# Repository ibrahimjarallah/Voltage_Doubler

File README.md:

# Voltage Doubler — NE555 Based PCB

> A compact, single-supply voltage doubler circuit built around the NE555 timer IC.  
> Designed and laid out in **KiCad 9.0** — schematic + 2-layer PCB with full fabrication outputs.

---

## 📸 3D Views

| Front | Back |
|:---:|:---:|
|  |  |

## 🖼️ PCB Layout (2D)

| Front | Back |
|:---:|:---:|
|  |  |

## 🟤 PCB Layout — Copper Fill (2D)

| Front | Back |
|:---:|:---:|
|  |  |

## 📐 Schematic

---

## ⚡ Specifications

| Parameter         | Value                        |
|-------------------|------------------------------|
| Input Voltage     | 5V DC                        |
| Output Voltage    | ~8.6V DC (no load)           |
| Topology          | Villard Cascade (diode-cap)  |
| Oscillator        | NE555 astable mode           |
| Oscillation Freq  | ~600 Hz                      |
| Output Ripple     | Dependent on load current    |
| PCB Layers        | 2                            |
| Designed With     | KiCad 9.0.7                  |

> **Note:** Output voltage sags under load due to 22µF storage capacitors and NE555 drive limitations.  
> Suitable for light-load, low-current applications.

---

## 🔧 How It Works

The **NE555** is configured in **astable (free-running) mode**, generating a ~600 Hz square wave set by:

- **R1** (10kΩ) and **R2** (33kΩ) — timing resistors
- **C1/C2** (10nF) — timing capacitors

This switching signal drives a **Villard cascade** charge pump:

1. On the rising edge, **C3** (22µF) charges through **D1** (1N4007)
2. On the falling edge, **C4** (22µF) charges to the sum of Vin + Vc3 through **D2** (1N4007)
3. Result: output voltage ≈ **2 × Vin − 2 × Vf** ≈ **8.6V** (where Vf ≈ 0.7V per diode)

---

## 📦 Bill of Materials

| ID | Designator | Description | Quantity | Footprint |
|----|------------|-------------|----------|-----------|
| 1 | U1 | NE555D Timer IC | 1 | SO-8 3.9×4.9mm P1.27mm |
| 2 | R1 | Resistor 10.0kΩ | 1 | Axial DIN0204 L3.6mm P5.08mm |
| 3 | R2 | Resistor 33.0kΩ | 1 | Axial DIN0204 L3.6mm P5.08mm |
| 4 | D1, D2 | Diode 1N4007 | 2 | D 5W P10.16mm Horizontal |
| 5 | C1, C2 | Capacitor 10nF (ceramic) | 2 | Disc D3.0mm W1.6mm P2.50mm |
| 6 | C3, C4 | Capacitor 22µF (electrolytic) | 2 | Radial D4.0mm H5.0mm P1.50mm |
| 7 | J1, J2 | 1×2 Pin Header connector | 2 | PinHeader 1×2 P1.00mm Horizontal |

---

## 📁 Repository Structure

```
Voltage_Doubler/
├── Voltage_Doubler.kicad_pro     # KiCad project file
├── Voltage_Doubler.kicad_sch     # Schematic
├── Voltage_Doubler.kicad_pcb     # PCB layout
├── Voltage_Doubler.kicad_dru     # Design rules
├── Voltage_Doubler.net           # Netlist
├── BOM/
│   └── Voltage_Doubler.csv       # Bill of materials
├── gerbers/                      # Fabrication Gerber files
│   ├── Voltage_Doubler-F_Cu.gbr
│   ├── Voltage_Doubler-B_Cu.gbr
│   ├── Voltage_Doubler-F_Mask.gbr
│   ├── Voltage_Doubler-B_Mask.gbr
│   ├── Voltage_Doubler-F_Silkscreen.gbr
│   ├── Voltage_Doubler-B_Silkscreen.gbr
│   ├── Voltage_Doubler-F_Paste.gbr
│   ├── Voltage_Doubler-B_Paste.gbr
│   ├── Voltage_Doubler-Edge_Cuts.gbr
│   └── Voltage_Doubler-job.gbrjob
├── drills/
│   ├── Voltage_Doubler-PTH.drl   # Plated through-holes
│   └── Voltage_Doubler-NPTH.drl  # Non-plated through-holes
└── 3D_VIEW/
    ├── Voltage_Doubler_Front.png
    └── Voltage_Doubler_Back.png
├── 2D_VIEW/
│   ├── 2d_view_front.png
│   ├── 2d_view_back.png
│   ├── 2d_view_front_filled.png
│   └── 2d_view_back_filled.png
└── Schematic_view/
    └── Schematic_view.png
```

---

## 🖥️ Opening the Project

1. Install [KiCad 9.0+](https://www.kicad.org/download/)
2. Clone this repository:
   ```bash
   git clone https://github.com/ibrahimjarallah/Voltage_Doubler.git
   ```
3. Open `Voltage_Doubler.kicad_pro` in KiCad

---

## 🏭 Fabrication

All fabrication outputs are ready in the `gerbers/` and `drills/` folders.  
Compatible with standard PCB manufacturers (JLCPCB, PCBWay, OSHPark, etc.).

- Load `Voltage_Doubler-job.gbrjob` directly into any Gerber viewer or fab upload portal
- Drill files: `PTH` (plated) and `NPTH` (non-plated) provided separately

---

## 📄 License

This project is licensed under the **MIT License**.  
You are free to use, modify, and distribute it with attribution.

---

## 👤 Author

**Ibrahim Jarallah**  
GitHub: [ibrahimjarallah] : https://github.com/ibrahimjarallah \
LinkedIn: [ibrahimjarallah] : https://www.linkedin.com/in/ibrahim-jarallah

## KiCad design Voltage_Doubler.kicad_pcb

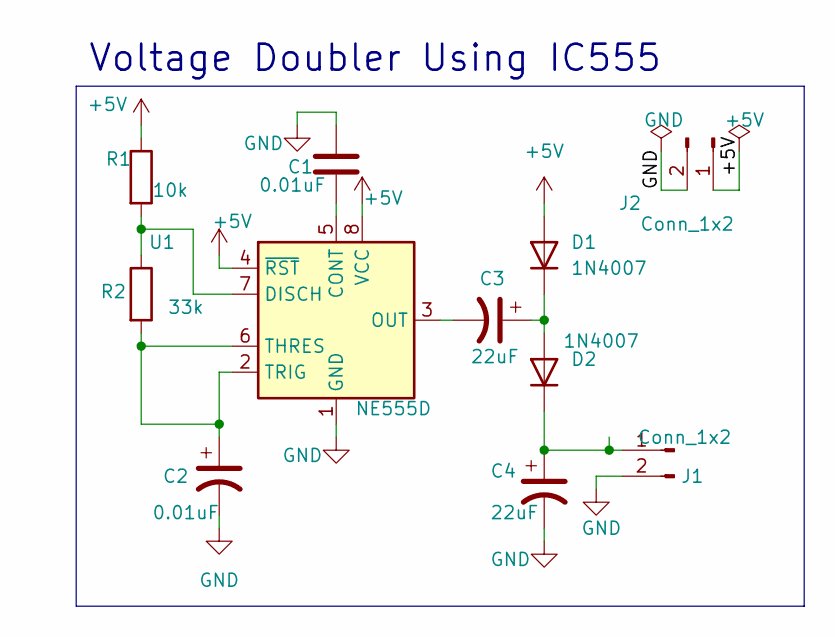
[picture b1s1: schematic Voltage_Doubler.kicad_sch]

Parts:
C1, C2: 0.01uF; C_Disc_D3.0mm_W1.6mm_P2.50mm
C3, C4: 22uF; C_Radial_D4.0mm_H5.0mm_P1.50mm
D1, D2: 1N4007; D_5W_P10.16mm_Horizontal
J1, J2: Conn_1x2; PinHeader_1x02_P1.00mm_Horizontal
R1: 10k; R_Axial_DIN0204_L3.6mm_D1.6mm_P5.08mm_Horizontal
R2: 33k; R_Axial_DIN0204_L3.6mm_D1.6mm_P5.08mm_Horizontal
U1: NE555D; SO-8_3.9x4.9mm_P1.27mm

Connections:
+5V: D1.2 (A), J2.1, R1.1, U1.4 (~RST), U1.8 (VCC)
GND: C1.1, C2.2, C4.2, J1.2, J2.2, U1.1 (GND)
unnamed: C3.1, D1.1 (K), D2.2 (A)
unnamed: C4.1, D2.1 (K), J1.1
unnamed: C1.2, U1.5 (CONT)
unnamed: R1.2, R2.1, U1.7 (DISCH)
unnamed: C3.2, U1.3 (OUT)
unnamed: C2.1, R2.2, U1.2 (TRIG), U1.6 (THRES)

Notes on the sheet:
Voltage Doubler Using IC555

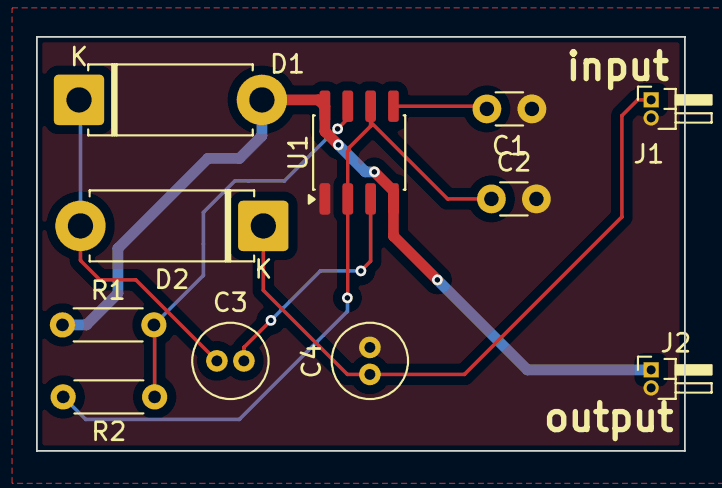
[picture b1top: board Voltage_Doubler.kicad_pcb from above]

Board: 2 copper layers, 36.0 x 23.0 mm, 11 parts (0 on the bottom side), 8 nets.

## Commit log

2026-02-27 Initial commit: NE555 voltage doubler schematic, PCB layout, Gerbers, BOM, and documentation
2026-02-27 added 2d view
2026-02-27 updated 2d view
2026-02-27 updated personal info
2026-02-27 updated pcb info
2026-03-09 Update: added front/back 2D views, copper fill views, schematic view, updated 3D views and PCB/schematic
2026-03-09 updated pcb views
